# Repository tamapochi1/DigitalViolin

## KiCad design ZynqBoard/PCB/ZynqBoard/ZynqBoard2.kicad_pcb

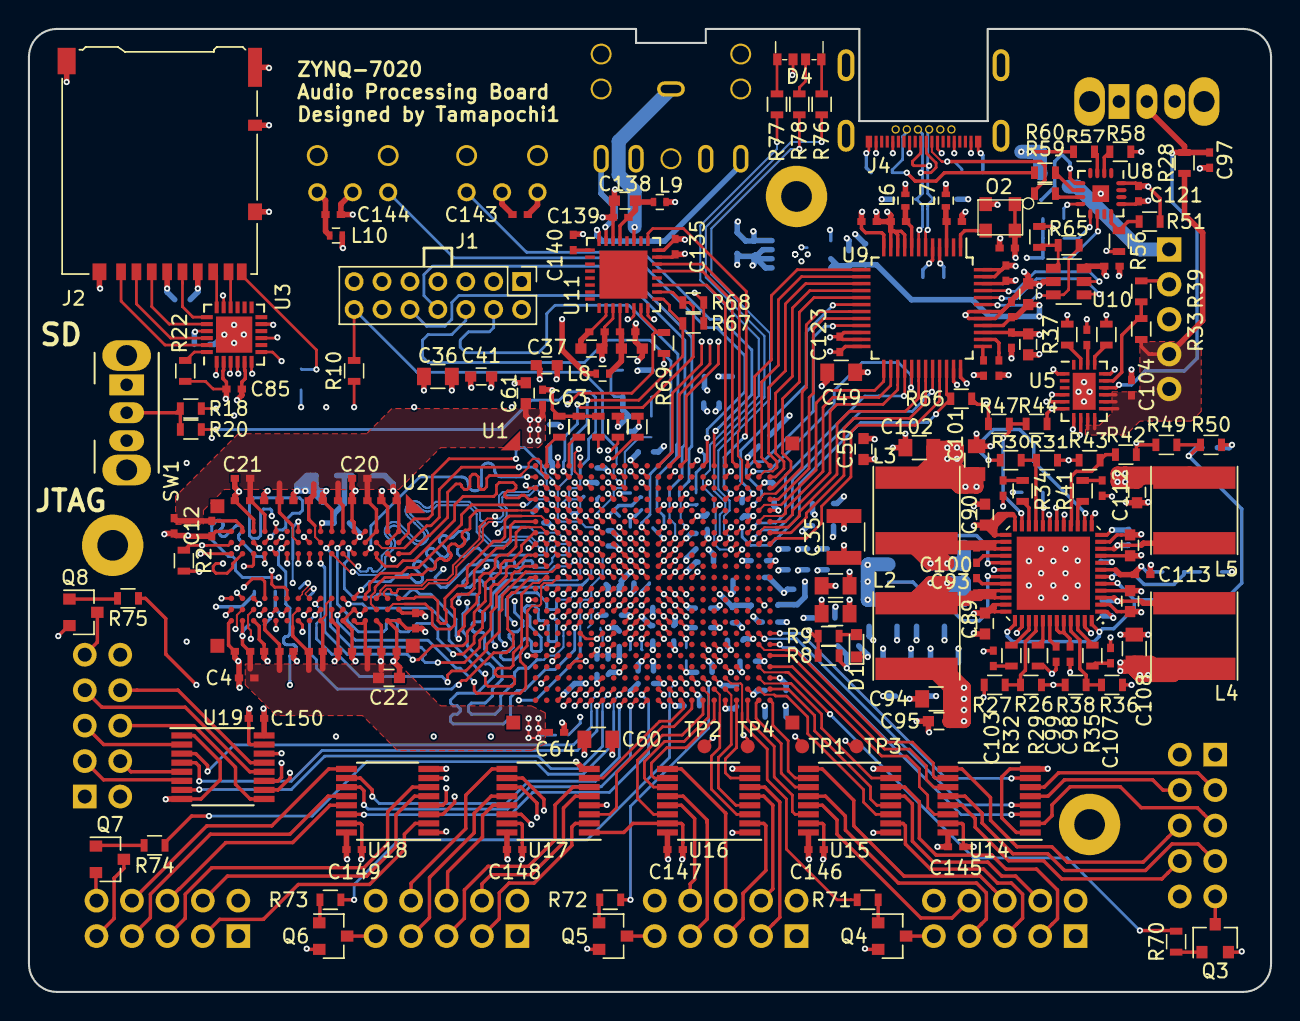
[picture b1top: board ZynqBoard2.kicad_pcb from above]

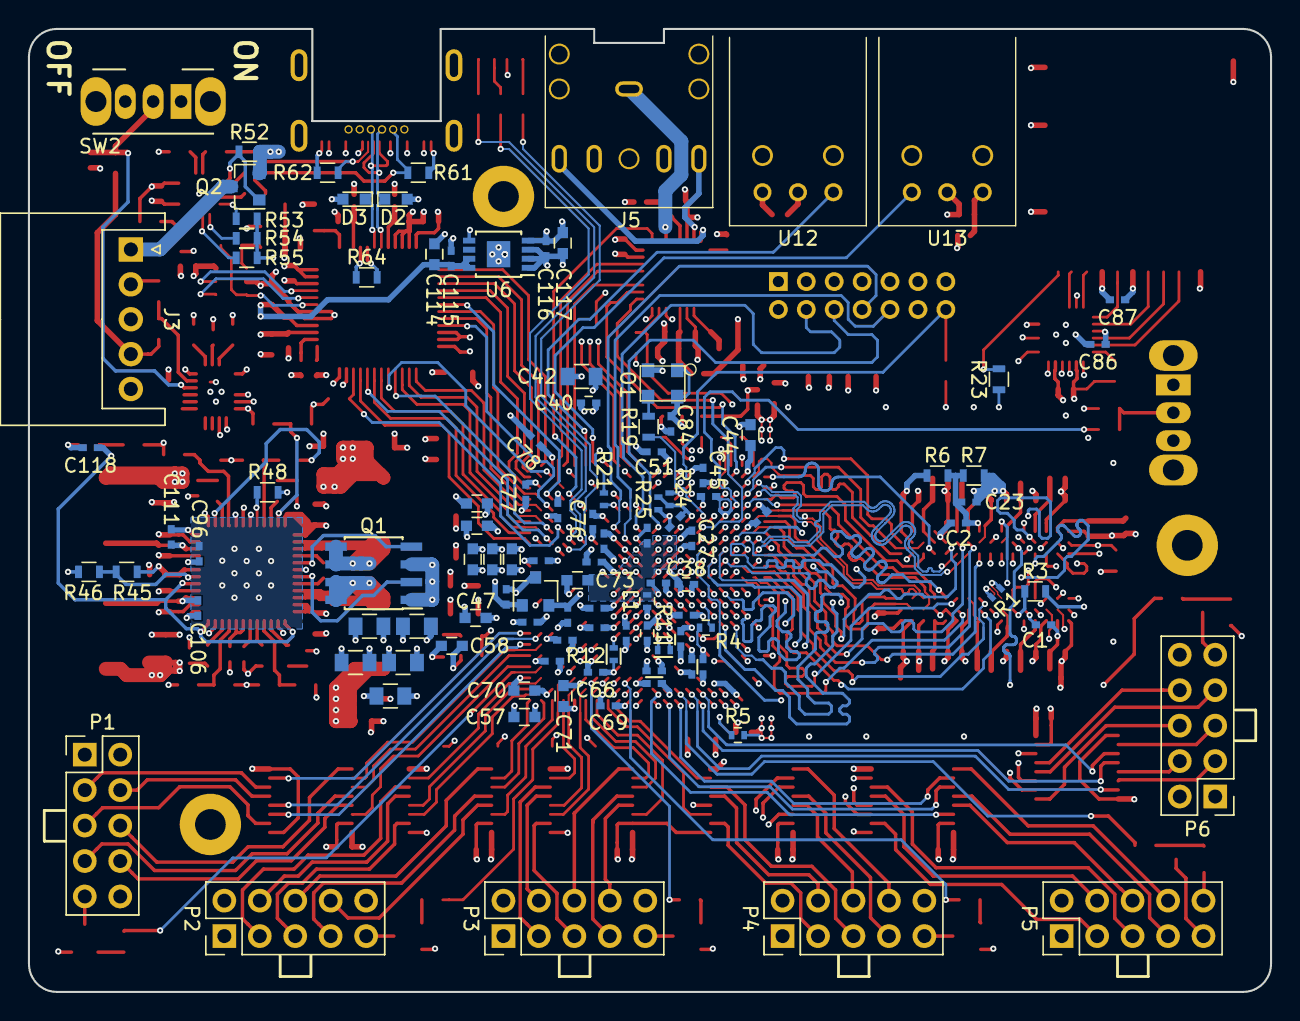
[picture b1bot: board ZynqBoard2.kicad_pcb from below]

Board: 6 copper layers, 89.0 x 69.0 mm, 288 parts (108 on the bottom side), 295 nets.

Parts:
C1, C2, C23, C88, C109: 10n; C_0402_NoSilk
C3, C82, C83, C84, C85, C86, C87, C93, C100, C104, C106, C111, C115, C116, C119, C120, C122, C123, C124, C126, C127, C128, C130, C131, C132, C133, C134, C135, C137, C139, C141, C143, C144, C145, C146, C147, C148, C149, C150: 0.1u; C_0402_NoSilk
C4, C5, C6, C7, C8, C9, C10, C11, C12, C13, C14, C15, C16, C17, C18, C19: 47n; C_0402_NoSilk
C20, C21, C26, C27, C28, C29, C30, C31, C32, C45, C46, C51, C53, C54, C55, C56, C62, C63, C64, C65, C66, C67, C68, C69, C74, C75, C76, C77, C78: 0.47u; C_0402_NoSilk
C22, C25, C33, C34, C37, C41, C44, C47, C50, C57, C58, C61, C70, C71, C79, C80, C95, C114, C117, C125, C129, C136, C138: 4.7u; C_0603
C24, C36, C43, C48, C49, C59, C60, C72, C81: 100u; C_0805
C35: 330u; C_1210
C38, C39, C40: 0.47u; C_0402
C42, C52, C94, C101, C102: 47u; C_0805
C73, C89, C90, C91, C92, C112: 10u; C_0603
C96, C97, C98, C99, C113, C121, C140: 1u; C_0402_NoSilk
C103, C105: 2.7n; C_0402_NoSilk
C107: 1n; C_0402_NoSilk
C108: 22u; C_0805
C110: 3.9n; C_0402_NoSilk
C118: 2.2n; C_0402_NoSilk
C142: 2.2u; C_0603
D1: DONE(BLUE); LED_0603
D2, D3: PGB1010603MR; LED_0603
D4: CL-425
J1: JTAG-HS3; Pin_Header_Straight_2x07_Pitch2.00mm
J2: Hirose_DM3AT; Hirose_DM3AT-SF-PEJM5
J3: Battery; JST_XH_S05B-XH-A_05x2.50mm_Angled
J4: USB_C_Receptacle; CX70M-24P1
J5: 35RAPC2BHN2; 35RAPC
L1, L6, L7, L8, L9, L10: 600ohm@100MHz; L_0402
L2, L3: 1.5uH; L_Taiyo-Yuden_NR-60xx
L4, L5: 3.3u; L_Taiyo-Yuden_NR-60xx
O1: DSC1001CI5-033.3333; DSC1001_CDFN-4_3.2x2.5
O2: DSC1001CL2-012.0000; DSC1001_CDFN-4_3.2x2.5
P1: Universal I/F 1; Pin_Header_Straight_2x05_Pitch2.54mm
P2: Universal I/F 2; Pin_Header_Straight_2x05_Pitch2.54mm
P3: Universal I/F 3; Pin_Header_Straight_2x05_Pitch2.54mm
P4: Universal I/F 4; Pin_Header_Straight_2x05_Pitch2.54mm
P5: Universal I/F 5; Pin_Header_Straight_2x05_Pitch2.54mm
P6: Universal I/F 6; Pin_Header_Straight_2x05_Pitch2.54mm
Q1: FDS9926A; SOIC-8_3.9x4.9mm_Pitch1.27mm
Q2: Si2369DS; SOT-23
Q3, Q4, Q5, Q6, Q7, Q8: IRLML6344TRPbF; SOT-23
R1: 80; R_0402_NoSilk
R2, R10, R22, R33, R34, R37, R47, R66, R69: 4.7k; R_0603
R3: 240; R_0603
R4, R5: 80; R_0402
R6, R7, R28, R31, R50, R53, R54, R55, R57, R58, R59, R60, R63: 10k; R_0603
R8, R39, R70, R71, R72, R73, R74, R75, R76, R77, R78: 1k; R_0603
R9: 220; R_0603
R11, R12: 4.7k; R_0402_NoSilk
R13, R14, R15, R16, R17, R18, R20, R40, R41, R44, R48, R52: 20k; R_0603
R19: 24; R_0603
R21: 40.2; R_0402_NoSilk
R23: 47k; R_0603
R24, R25: 10k; R_0402_NoSilk
R26, R43: 10.2k; R_0603
R27: 31.6k; R_0603
R29: 39.2k; R_0603
R30: 2.49k; R_0603
R32: 66.5k; R_0603
R35: 8.87k; R_0603
R36: 19.6k; R_0603
R38: 28.7k; R_0603
R42: 12.7k; R_0603
R45: 4.99k; R_0603
R46: 1.91k; R_0603
R49: 8.06k; R_0603
R51: 35.7k; R_0603
R56, R61, R62: 5.1k; R_0603
R64: 12k; R_0603
R65: 2k; R_0603
R67, R68: 3.3k; R_0603
SW1: Select_SD/JTAG; SW_CuK_OS102011MA1QN1_SPDT_Angled
SW2: SW_SPDT; SW_CuK_OS102011MA1QN1_SPDT_Angled
TP1: TEST1; Measurement_Point_Round-SMD-Pad_Small
TP2: TEST2; Measurement_Point_Round-SMD-Pad_Small
TP3: TEST3; Measurement_Point_Round-SMD-Pad_Small
TP4: TEST4; Measurement_Point_Round-SMD-Pad_Small
U1: XC7Z020-1CLG484C; BGA-484_22x22_19.0x19.0mm
U2: IS43TR16256AL-125KBL; BGA-96_2x3x16_9.0x13.0mm_Pitch0.8mm
U3: TXS02612RTWR; QFN-24-1EP_4x4mm_Pitch0.5mm
U4: ADP5052ACPZ-R7; LFCSP-VQ-48-1EP_7x7mm_Pitch0.5mm
U5: TPS25940ARVC; QFN-20-1EP_3x4mm_Pitch0.5mm
U6: ADP124ARHZ-3.3-R7; MSOP-8-1EP_3x3mm_Pitch0.65mm
U7: REF3012; SOT-23
U8: UTC2000; QFN-16-1EP_3x3mm_Pitch0.5mm
U9: FT-232H; LQFP-48_7x7mm_Pitch0.5mm
U10: 93LC56BT-I_OTCT; SOT-23-6
U11: AK4373EN; QFN-32-1EP_5x5mm_Pitch0.5mm
U12: PLT133_T10W; PLT133
U13: PLR135_T10; PLT133
U14, U15, U16, U17, U18, U19: M74HC365; TSSOP-16_4.4x5mm_Pitch0.65mm

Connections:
+1V0: C24.1, C25.1, C26.1, C27.1, C28.1, C29.1, C30.1, C31.1, C32.1, C33.1, C34.1, C35.1, C46.1, C47.1, C48.1, C101.1, C102.1, L3.1, R30.1, U1.G8, U1.H9, U1.H11, U1.J8, U1.J10, U1.J12, U1.J14, U1.K13, U1.L8, U1.L14, U1.M13, U1.N8, U1.N14, U1.P13, U1.R8, U1.R14, U4.14
+1V8: C36.1, C37.1, C38.1, C39.1, C40.1, C41.1, C42.1, C49.1, C50.1, C51.1, C85.1, C112.1, L1.1, L5.1, R10.1, R23.1, R24.1, R42.1, R49.1, R53.2, R54.2, R55.2, U1.A10, U1.B13, U1.D9, U1.E12, U1.G9, U1.K9, U1.L10, U1.M9, U1.N10, U1.P9, U1.P11, U1.R10, U1.T9, U3.5
+1V35: C1.1, C4.1, C5.1, C6.1, C7.1, C8.1, C9.1, C10.1, C11.1, C12.1, C13.1, C14.1, C15.1, C16.1, C17.1, C18.1, C19.1, C20.1, C21.1, C22.1, C60.1, C61.1, C62.1, C63.1, C64.1, C65.1, C108.1, L4.1, R5.2, R6.1, R36.1, U1.E2, U1.F5, U1.H1, U1.J4, U1.K7, U1.M3, U1.N6, U1.R2, U1.V1, U2.A1, U2.A8, U2.B2, U2.C1, U2.C9, U2.D2, U2.D9, U2.E9, U2.F1, U2.G7, U2.H2, U2.H9, U2.K2, U2.K8, U2.N1, U2.N9, U2.R1, U2.R9
+3.3VA: C122.1, C123.1, C124.1, C125.1, C126.1, C131.1, C133.1, L6.1, L7.1, O2.1, O2.4, R63.1, U9.12, U9.24, U9.39, U9.46, U10.6
+3V3: C43.1, C44.1, C45.1, C52.1, C53.1, C54.1, C55.1, C56.1, C57.1, C58.1, C59.1, C66.1, C67.1, C68.1, C69.1, C70.1, C71.1, C72.1, C75.1, C76.1, C77.1, C78.1, C79.1, C80.1, C81.1, C84.1, C86.1, C87.1, C94.1, C95.1, C96.1, C135.1, C143.1, C145.1, C146.1, C147.1, C148.1, C149.1, C150.1, D4.2, J1.2, J2.4, L2.2, L10.1, O1.1, O1.4, R8.1, R11.1, R12.2, R13.2, R27.2, R48.2, R67.1, R68.1, SW1.1, U1.A20, U1.AA10, U1.AA20, U1.AB3, U1.AB13, U1.B3, U1.C6, U1.C16, U1.D19, U1.E22, U1.F15, U1.G18, U1.H21, U1.R12, U1.T5, U1.T7, U1.T8, U1.T10, U1.T13, U1.U8, U1.U18, U1.V11, U1.V21, U1.W4, U1.W14, U1.Y7, U1.Y17, U3.17, U3.21, U4.8, U6.5, U11.6, U11.15, U12.2, U14.16, U15.16, U16.16, U17.16, U18.16, U19.16
+5V: C89.1, C90.1, C91.1, C92.1, C114.1, C115.1, C129.1, C130.1, P1.1, P2.1, P3.1, P4.1, P5.1, P6.1, R44.1, U4.4, U4.9, U4.24, U4.25, U4.35, U4.36, U5.4, U5.5, U5.6, U5.7, U5.8, U6.7, U6.8, U9.40
/Config/BOOT_MODE0: R18.1, U1.A3
/Config/BOOT_MODE1: R15.1, U1.F6
/Config/BOOT_MODE2: R20.1, U1.E4
/Config/BOOT_MODE3: R16.1, U1.A2
/Config/BOOT_MODE4: R17.1, U1.A4
/Config/DONE: R8.2, R9.1, U1.T12
/Config/PS_CLK: R19.2, U1.F7
/Config/TCK: J1.6, U1.G11
/Config/TDI: J1.10, U1.H13
/Config/TDO: J1.8, U1.G14
/Config/TMS: J1.4, U1.G12
/Config/VMODE0: R14.1, U1.D5
/Config/VMODE1: R13.1, U1.E5
/DDR/DDR_A0: U1.M4, U2.N3
/DDR/DDR_A1: U1.M5, U2.P7
/DDR/DDR_A2: U1.K4, U2.P3
/DDR/DDR_A3: U1.L4, U2.N2
/DDR/DDR_A4: U1.K6, U2.P8
/DDR/DDR_A5: U1.K5, U2.P2
/DDR/DDR_A6: U1.J7, U2.R8
/DDR/DDR_A7: U1.J6, U2.R2
/DDR/DDR_A8: U1.J5, U2.T8
/DDR/DDR_A9: U1.H5, U2.R3
/DDR/DDR_A10: U1.J3, U2.L7
/DDR/DDR_A11: U1.G5, U2.R7
/DDR/DDR_A12: U1.H4, U2.N7
/DDR/DDR_A13: U1.F4, U2.T3
/DDR/DDR_A14: U1.G4, U2.T7
/DDR/DDR_BA0: U1.L7, U2.M2
/DDR/DDR_BA1: U1.L6, U2.N8
/DDR/DDR_BA2: U1.M6, U2.M3
/DDR/DDR_CAS: U1.P3, U2.K3
/DDR/DDR_CKE: U1.V3, U2.K9
/DDR/DDR_CK_N: R1.2, U1.N5, U2.K7
/DDR/DDR_CK_P: R1.1, U1.N4, U2.J7
/DDR/DDR_CS: U1.P6, U2.L2
/DDR/DDR_DM0: U1.H3, U2.E7
/DDR/DDR_DM1: U1.B1, U2.D3
/DDR/DDR_DQ0: U1.G2, U2.E3
/DDR/DDR_DQ1: U1.L2, U2.F7
/DDR/DDR_DQ2: U1.J1, U2.F2
/DDR/DDR_DQ3: U1.L3, U2.F8
/DDR/DDR_DQ4: U1.G1, U2.H3
/DDR/DDR_DQ5: U1.L1, U2.H8
/DDR/DDR_DQ6: U1.K1, U2.G2
/DDR/DDR_DQ7: U1.K3, U2.H7
/DDR/DDR_DQ8: U1.E3, U2.D7
/DDR/DDR_DQ9: U1.D1, U2.C3
/DDR/DDR_DQ10: U1.E1, U2.C8
/DDR/DDR_DQ11: U1.D3, U2.C2
/DDR/DDR_DQ12: U1.F2, U2.A7
/DDR/DDR_DQ13: U1.C3, U2.A2
/DDR/DDR_DQ14: U1.F1, U2.B8
/DDR/DDR_DQ15: U1.B2, U2.A3
/DDR/DDR_DQS_0_N: U1.J2, U2.G3
/DDR/DDR_DQS_0_P: U1.H2, U2.F3
/DDR/DDR_DQS_1_N: U1.D2, U2.B7
/DDR/DDR_DQS_1_P: U1.C2, U2.C7
/DDR/DDR_DRST: R2.1, U1.F3, U2.T2
/DDR/DDR_ODT: U1.P5, U2.K1
/DDR/DDR_RAS: U1.R5, U2.J3
/DDR/DDR_VREF: C1.2, C2.1, C3.1, C23.1, R6.2, R7.1, U1.H7, U1.P7, U2.H1, U2.M8
/DDR/DDR_WE: U1.R4, U2.L3
/I/F/1_HRXD: P1.7, U14.12
/I/F/1_HSCK: P1.6, U14.9
/I/F/1_HTXD: P1.8, U14.13
/I/F/1_SRXD: P1.4, U14.5
/I/F/1_SSCK: P1.3, U14.6
/I/F/1_STXD: P1.5, U14.2
/I/F/2_HRXD: P2.7, U15.12
/I/F/2_HSCK: P2.6, U15.9
/I/F/2_HTXD: P2.8, U15.13
/I/F/2_SRXD: P2.4, U15.5
/I/F/2_SSCK: P2.3, U15.6
/I/F/2_STXD: P2.5, U15.2
/I/F/3_HRXD: P3.7, U16.12
/I/F/3_HSCK: P3.6, U16.9
/I/F/3_HTXD: P3.8, U16.13
/I/F/3_SRXD: P3.4, U16.5
/I/F/3_SSCK: P3.3, U16.6
/I/F/3_STXD: P3.5, U16.2
/I/F/4_HRXD: P4.7, U17.12
/I/F/4_HSCK: P4.6, U17.13
/I/F/4_HTXD: P4.8, U17.9
/I/F/4_SRXD: P4.4, U17.5
/I/F/4_SSCK: P4.3, U17.2
/I/F/4_STXD: P4.5, U17.6
/I/F/5_HRXD: P5.7, U18.12
/I/F/5_HSCK: P5.6, U18.13
/I/F/5_HTXD: P5.8, U18.9
/I/F/5_SRXD: P5.4, U18.5
/I/F/5_SSCK: P5.3, U18.2
/I/F/5_STXD: P5.5, U18.6
/I/F/6_HRXD: P6.7, U19.12
/I/F/6_HSCK: P6.6, U19.9
/I/F/6_HTXD: P6.8, U19.13
/I/F/6_SRXD: P6.4, U19.5
/I/F/6_SSCK: P6.3, U19.6
/I/F/6_STXD: P6.5, U19.2
/PL_IO/B: R78.1, U1.H18
/PL_IO/G: R77.1, U1.H19
/PL_IO/R: R76.1, U1.H17
/PL_IO/TEST1: TP1.1, U1.W18
/PL_IO/TEST2: TP2.1, U1.U16
/PL_IO/TEST3: TP3.1, U1.U17
/PL_IO/TEST4: TP4.1, U1.V17
/PowerSupply/SW_EN: C97.1, R28.2, SW2.2, U5.14
/PowerSupply/VREG: C98.1, U4.43, U4.44
/SD/SD_CD: J2.9, R23.2, U1.B10
/SD/SD_CLK: R21.1, U3.9
/SD/SD_CMD: U1.C8, U3.4
/SD/SD_D0: U1.D8, U3.6
/SD/SD_D1: U1.B11, U3.7
/SD/SD_D2: U1.E13, U3.1
/SD/SD_D3: U1.B9, U3.3
/SD/VREF0V9: C88.1, R24.2, R25.1, U1.F8
/USB/DM: D3.1, J4.A7, J4.B7, U9.6
/USB/DP: D2.1, J4.A6, J4.B6, U9.7
/USB/VPHY: C134.1, L7.2, U9.3
/USB/VPLL: C132.1, L6.2, U9.8
GND: C2.2, C3.2, C4.2, C5.2, C6.2, C7.2, C8.2, C9.2, C10.2, C11.2, C12.2, C13.2, C14.2, C15.2, C16.2, C17.2, C18.2, C19.2, C20.2, C21.2, C22.2, C23.2, C24.2, C25.2, C26.2, C27.2, C28.2, C29.2, C30.2, C31.2, C32.2, C33.2, C34.2, C35.2, C36.2, C37.2, C38.2, C39.2, C40.2, C41.2, C42.2, C43.2, C44.2, C45.2, C46.2, C47.2, C48.2, C49.2, C50.2, C51.2, C52.2, C53.2, C54.2, C55.2, C56.2, C57.2, C58.2, C59.2, C60.2, C61.2, C62.2, C63.2, C64.2, C65.2, C66.2, C67.2, C68.2, C69.2, C70.2, C71.2, C72.2, C73.2, C74.2, C75.2, C76.2, C77.2, C78.2, C79.2, C80.2, C81.2, C82.2, C83.2, C84.2, C85.2, C86.2, C87.2, C88.2, C89.2, C90.2, C91.2, C92.2, C94.2, C95.2, C96.2, C97.2, C98.2, C99.2, C101.2, C102.2, C103.1, C104.2, C105.1, C107.1, C108.2, C109.2, C110.1, C112.2, C113.2, C114.2, C115.2, C116.2, C117.2, C118.2, C119.2, C120.2, C121.2, C122.2, C123.2, C124.2, C125.2, C126.2, C127.2, C128.2, C129.2, C130.2, C131.2, C132.2, C133.2, C134.2, C135.2, C136.2, C137.2, C138.2, C139.2, C140.2, C141.2, C142.2, C143.2, C144.2, C145.2, C146.2, C147.2, C148.2, C149.2, C150.2, D1.1, D2.2, D3.2, J1.1, J1.3, J1.5, J1.7, J1.9, J1.11, J1.13, J2.6, J2.10, J2.11, J3.2, J3.3, J4.A1, J4.A12, J4.B1, J4.B12, J4.S1, O1.2, O2.2, P1.2, P1.10, P2.2, P2.10, P3.2, P3.10, P4.2, P4.10, P5.2, P5.10, P6.2, P6.10, Q1.1, Q1.3, Q3.2, Q4.2, Q5.2, Q6.2, Q7.2, Q8.2, R2.2, R3.2, R4.2, R7.2, R14.2, R15.2, R16.2, R17.2, R22.2, R25.2, R26.2, R29.1, R31.2, R37.2, R38.2, R39.2, R40.2, R43.2, R46.2, R47.2, R50.2, R56.2, R61.2, R62.2, R64.1, R66.2, R69.2, SW1.3, SW2.3, U1.A5, U1.A15, U1.AA5, U1.AA15, U1.AB8, U1.AB18, U1.B8, U1.B18, U1.C1, U1.C11, U1.C21, U1.D4, U1.D14, U1.E7, U1.E17, U1.F10, U1.F20, U1.G3, U1.H6, U1.H8, U1.H12, U1.H14, U1.H16, U1.J9, U1.J11, U1.J13, U1.J19, U1.K2, U1.K8, U1.K10, U1.K12, U1.K14, U1.K22, U1.L5, U1.L9, U1.L11, U1.L12, U1.L13, U1.L15, U1.M8, U1.M10, U1.M12, U1.M14, U1.M18, U1.N1, U1.N9, U1.N11, U1.N12, U1.N13, U1.N21, U1.P4, U1.P8, U1.P10, U1.P12, U1.P14, U1.R9, U1.R11, U1.R13, U1.R17, U1.T20, U1.U3, U1.U13, U1.V6, U1.V16, U1.W9, U1.W19, U1.Y2, U1.Y12, U1.Y22, U2.A9, U2.B1, U2.B3, U2.B9, U2.D1, U2.D8, U2.E1, U2.E2, U2.E8, U2.F9, U2.G1, U2.G8, U2.G9, U2.J2, U2.J8, U2.M1, U2.M9, U2.P1, U2.P9, U2.T1, U2.T9, U3.2, U3.11, U3.25, U4.2, U4.11, U4.13, U4.17, U4.18, U4.19, U4.30, U4.38, U4.47, U4.49, U5.1, U5.16, U5.21, U6.4, U6.9, U7.3, U8.13, U8.17, U9.4, U9.9, U9.10, U9.11, U9.22, U9.23, U9.35, U9.36, U9.41, U9.42, U9.47, U9.48, U10.2, U11.3, U11.8, U11.16, U11.22, U12.3, U13.2, U14.1, U14.8, U14.15, U15.1, U15.8, U15.15, U16.1, U16.8, U16.15, U17.1, U17.8, U17.15, U18.1, U18.8, U18.15, U19.1, U19.8, U19.15
HP_3V3: C116.1, C117.1, L8.1, L9.1, U6.1, U6.2, U6.3
HP_BCLK: U1.C19, U11.14
HP_LRCK: U1.A19, U11.13
HP_MCLK: U1.D18, U11.17
HP_RSTN: R69.1, U1.C5, U11.7
HP_SCL: R67.2, U1.G7, U11.9
HP_SDA: R68.2, U1.B4, U11.10
HP_SDT: U1.A18, U11.11
IF1_HRXD: U1.V22, U14.11
IF1_HSCK: U1.U21, U14.10
IF1_HTXD: U1.W22, U14.14
IF1_RST: R70.1, U1.W21
IF1_SRXD: U1.T21, U14.4
IF1_SSCK: U1.T22, U14.7
IF1_STXD: U1.U22, U14.3
IF2_HRXD: U1.AB21, U15.11
IF2_HSCK: U1.AB22, U15.10
IF2_HTXD: U1.AB20, U15.14
IF2_RST: R71.1, U1.Y18
IF2_SRXD: U1.AA22, U15.4
IF2_SSCK: U1.Y21, U15.7
IF2_STXD: U1.AA21, U15.3
IF3_HRXD: U1.AA16, U16.11
IF3_HSCK: U1.AB17, U16.10
IF3_HTXD: U1.AB16, U16.14
IF3_RST: R72.1, U1.Y16
IF3_SRXD: U1.AA18, U16.4
IF3_SSCK: U1.AB19, U16.7
IF3_STXD: U1.AA17, U16.3
IF4_HRXD: U1.Y14, U17.11
IF4_HSCK: U1.AA14, U17.14
IF4_HTXD: U1.AA13, U17.10
IF4_RST: R73.1, U1.Y13
IF4_SRXD: U1.Y15, U17.4
IF4_SSCK: U1.AB15, U17.3
IF4_STXD: U1.AB14, U17.7
IF5_HRXD: U1.AB10, U18.11
IF5_HSCK: U1.AA11, U18.14
IF5_HTXD: U1.AB9, U18.10
IF5_RST: R74.1, U1.AA9
IF5_SRXD: U1.AA12, U18.4
IF5_SSCK: U1.AB12, U18.3
IF5_STXD: U1.AB11, U18.7
IF6_HRXD: U1.AA6, U19.11
IF6_HSCK: U1.AB6, U19.10
IF6_HTXD: U1.AB5, U19.14
IF6_RST: R75.1, U1.AB4
IF6_SRXD: U1.AB7, U19.4
IF6_SSCK: U1.AA8, U19.7
IF6_STXD: U1.AA7, U19.3
unnamed: C73.1, C74.1, L1.2, U1.H10
unnamed: C93.1, U4.32
unnamed: C93.2, L2.1, Q1.7, Q1.8, U4.33, U4.34
unnamed: C99.1, U4.42
unnamed: C100.1, L3.2, Q1.5, Q1.6, U4.26, U4.27
unnamed: C100.2, U4.28
unnamed: C103.2, R32.1
unnamed: C105.2, R34.1
unnamed: C106.1, U4.1
unnamed: C106.2, L4.2, U4.3
unnamed: C107.2, R35.1
unnamed: C109.1, U5.18
unnamed: C110.2, R41.1
unnamed: C111.1, U4.12
unnamed: C111.2, L5.2, U4.10
unnamed: C118.1, R49.2, R50.1, U4.5, U4.37, U4.48
unnamed: C121.1, J4.A4, J4.A9, J4.B4, J4.B9, Q2.2, R51.1, R52.1, R57.1, R58.1, U8.16
unnamed: C127.1, U9.38
unnamed: C128.1, U9.37
unnamed: C136.1, C137.1, L8.2, U11.4
unnamed: C138.1, C139.1, L9.2, U11.21
unnamed: C140.1, U11.25
unnamed: C141.1, C142.1, U11.2
unnamed: C144.1, L10.2, U13.1
unnamed: D1.2, R9.2
unnamed: D4.1, R77.2
unnamed: D4.3, R78.2
unnamed: D4.4, R76.2
unnamed: J2.1, U3.23
unnamed: J2.2, U3.22
unnamed: J2.3, U3.20
unnamed: J2.5, U3.19
unnamed: J2.7, U3.18
unnamed: J2.8, U3.16
unnamed: J3.1, Q2.3
unnamed: J4.A5, R59.1, R62.1
unnamed: J4.B5, R60.1, R61.1
unnamed: J5.1, U11.19
unnamed: J5.2, U11.24
unnamed: J5.3, U11.23
unnamed: O1.3, R19.1
unnamed: O2.3, U9.1
unnamed: P1.9, Q3.3
unnamed: P2.9, Q4.3
unnamed: P3.9, Q5.3
unnamed: P4.9, Q6.3
unnamed: P5.9, Q7.3
unnamed: P6.9, Q8.3
unnamed: Q1.2, U4.31
unnamed: Q1.4, U4.29
unnamed: Q2.1, R52.2, U8.5
unnamed: Q3.1, R70.2
unnamed: Q4.1, R71.2
unnamed: Q5.1, R72.2
unnamed: Q6.1, R73.2
unnamed: Q7.1, R74.2
unnamed: Q8.1, R75.2
unnamed: R3.1, U2.L8
unnamed: R4.1, U1.N7
unnamed: R5.1, U1.M7
unnamed: R11.2, U1.T11
unnamed: R12.1, U1.T14
unnamed: R18.2, R20.2, SW1.2
unnamed: R21.2, U1.E14
unnamed: R22.1, U3.24
unnamed: R26.1, R27.1, U4.40
unnamed: R29.2, U4.41
unnamed: R30.2, R31.1, U4.21
unnamed: R32.2, U4.39
unnamed: R33.2, R39.1, U5.15
unnamed: R34.2, U4.22
unnamed: R35.2, U4.46
unnamed: R36.2, R38.1, U4.45
unnamed: R37.1, U5.19
unnamed: R40.1, U5.17
unnamed: R41.2, U4.15
unnamed: R42.2, R43.1, U4.16
unnamed: R44.2, R47.1, U4.23
unnamed: R45.2, R46.1, U4.6
unnamed: R51.2, R56.1, U8.12
unnamed: R57.2, U8.3
unnamed: R58.2, U8.2
unnamed: R59.2, U8.7
unnamed: R60.2, U8.6
unnamed: R63.2, R65.1, U10.1
unnamed: R64.2, U9.5
unnamed: R65.2, U9.43, U10.3
unnamed: U9.44, U10.4
unnamed: U9.45, U10.5
PG_ALL: R48.1, U1.B5, U4.20
PS_SRST_B: J1.14, R10.2, U1.C9
SPDIF_IN: U1.A16, U13.3
SPDIF_OUT: U1.A17, U12.1
USB_CBUS7: U1.G22, U9.31
USB_CBUS8: U1.H20, U9.32
USB_CBUS9: U1.H22, U9.33
USB_CLK60: U1.B20, U9.29
USB_DBUS0: U1.A21, U9.13
USB_DBUS1: U1.A22, U9.14
USB_DBUS2: U1.B21, U9.15
USB_DBUS3: U1.B22, U9.16
USB_DBUS4: U1.C22, U9.17
USB_DBUS5: U1.D20, U9.18
USB_DBUS6: U1.D21, U9.19
USB_DBUS7: U1.D22, U9.20
USB_OE#: U1.G21, U9.30
USB_RD#: U1.F21, U9.26
USB_RSTN: R66.1, U1.G19, U9.34
USB_RXF#: U1.E20, U9.21
USB_SIWU#: U1.G20, U9.28
USB_TXE#: U1.E21, U9.25
USB_WR#: U1.F22, U9.27
VBUS_0.5A: R53.1, U1.A12, U8.8
VBUS_1.5A: R54.1, U1.A13, U8.9
VBUS_3.0A: R55.1, U1.A14, U8.10
VIN: C104.1, J3.4, J3.5, R28.1, R33.1, U5.9, U5.10, U5.11, U5.12, U5.13
XADC_1V8: C82.1, C113.1, C119.1, R45.1, U1.K11, U4.7, U7.1
XADC_1V25: C83.1, C120.1, U1.M11, U7.2

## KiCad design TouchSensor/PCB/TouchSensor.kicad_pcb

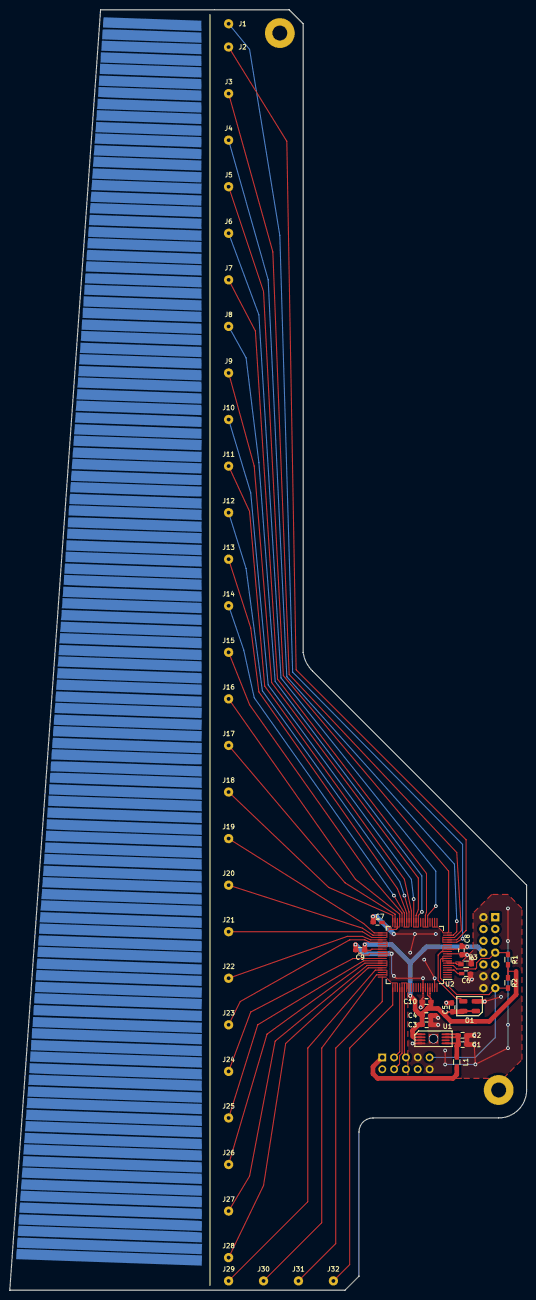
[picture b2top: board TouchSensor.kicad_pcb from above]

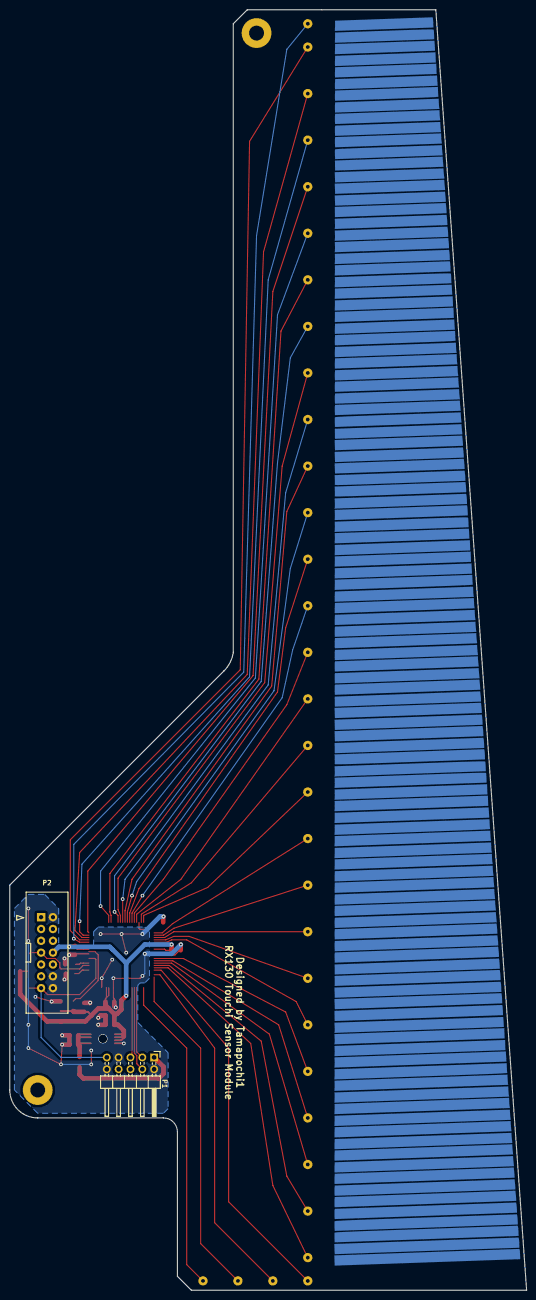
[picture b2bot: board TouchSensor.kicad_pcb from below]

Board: 2 copper layers, 111.0 x 275.0 mm, 51 parts (2 on the bottom side), 45 nets.

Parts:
C1, C4, C6: 4.7u; C_0603_HandSoldering
C2, C3, C5, C8, C9, C10: 0.1u; C_0603_HandSoldering
C7: 10n; C_0603_HandSoldering
J1: TS0; SolderWirePad_single_0-8mmDrill
J2: TS1; SolderWirePad_single_0-8mmDrill
J3: TS2; SolderWirePad_single_0-8mmDrill
J4: TS3; SolderWirePad_single_0-8mmDrill
J5: TS4; SolderWirePad_single_0-8mmDrill
J6: TS5; SolderWirePad_single_0-8mmDrill
J7: TS6; SolderWirePad_single_0-8mmDrill
J8: TS7; SolderWirePad_single_0-8mmDrill
J9: TS8; SolderWirePad_single_0-8mmDrill
J10: TS9; SolderWirePad_single_0-8mmDrill
J11: TS10; SolderWirePad_single_0-8mmDrill
J12: TS11; SolderWirePad_single_0-8mmDrill
J13: TS12; SolderWirePad_single_0-8mmDrill
J14: TS13; SolderWirePad_single_0-8mmDrill
J15: TS14; SolderWirePad_single_0-8mmDrill
J16: TS15; SolderWirePad_single_0-8mmDrill
J17: TS16; SolderWirePad_single_0-8mmDrill
J18: TS17; SolderWirePad_single_0-8mmDrill
J19: TS18; SolderWirePad_single_0-8mmDrill
J20: TS19; SolderWirePad_single_0-8mmDrill
J21: TS20; SolderWirePad_single_0-8mmDrill
J22: TS21; SolderWirePad_single_0-8mmDrill
J23: TS22; SolderWirePad_single_0-8mmDrill
J24: TS27; SolderWirePad_single_0-8mmDrill
J25: TS28; SolderWirePad_single_0-8mmDrill
J26: TS29; SolderWirePad_single_0-8mmDrill
J27: TS30; SolderWirePad_single_0-8mmDrill
J28: TS31; SolderWirePad_single_0-8mmDrill
J29: TS32; SolderWirePad_single_0-8mmDrill
J30, J31: TS33; SolderWirePad_single_0-8mmDrill
J32: TS34; SolderWirePad_single_0-8mmDrill
L1: BLM18KG331BH1D; L_0603_HandSoldering
O1: DSC1001CL5-008.0000T; 4-CDFN_3.2x2.5mm
P1: Conn_Universal; Pin_Header_Angled_2x05_Pitch2.54mm
P2: Conn_JTAG; JTAG
R1, R2, R3: 4.7k; R_0603_HandSoldering
U1: ADP124ARHZ-3.3-R7; 8-MSOP-EP_0.65mm
U2: R5F51303ADFN; QFP-80_12x12_Pitch0.5mm

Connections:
+3V3: C3.2, C4.2, C5.2, C8.2, C9.2, C10.2, O1.1, O1.4, P2.8, R1.1, R2.1, U1.1, U1.2, U1.3, U2.13, U2.48, U2.76, U2.77
+5V: L1.2, P1.1
/CLK8: O1.3, U2.12
/FINED: P2.7, R1.2, U2.6
/RES#: P1.9, P2.13, R2.2, U2.9
GND: C1.1, C2.1, C3.1, C4.1, C5.1, C6.2, C7.1, C8.1, C9.1, C10.1, O1.2, P1.2, P1.7, P1.10, P2.2, P2.12, P2.14, R3.2, U1.4, U1.EP, U2.11, U2.50, U2.74, U2.79
unnamed: C1.2, C2.2, L1.1, U1.5, U1.7, U1.8
unnamed: C6.1, U2.4
unnamed: C7.2, U2.38
unnamed: J1.1, U2.16
unnamed: J2.1, U2.17
unnamed: J3.1, U2.18
unnamed: J4.1, U2.19
unnamed: J5.1, U2.20
unnamed: J6.1, U2.25
unnamed: J7.1, U2.26
unnamed: J8.1, U2.29
unnamed: J9.1, U2.30
unnamed: J10.1, U2.31
unnamed: J11.1, U2.32
unnamed: J12.1, U2.33
unnamed: J13.1, U2.34
unnamed: J14.1, U2.35
unnamed: J15.1, U2.36
unnamed: J16.1, U2.37
unnamed: J17.1, U2.39
unnamed: J18.1, U2.40
unnamed: J19.1, U2.41
unnamed: J20.1, U2.42
unnamed: J21.1, U2.43
unnamed: J22.1, U2.44
unnamed: J23.1, U2.45
unnamed: J24.1, U2.52
unnamed: J25.1, U2.53
unnamed: J26.1, U2.54
unnamed: J27.1, U2.55
unnamed: J28.1, U2.56
unnamed: J29.1, U2.57
unnamed: J30.1, U2.59
unnamed: J31.1, U2.60
unnamed: J32.1, U2.61
unnamed: P1.3, U2.64
unnamed: P1.4, U2.65
unnamed: P1.5, U2.66
unnamed: R3.1, U2.7

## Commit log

2018-08-24 :boom::camel: Added .gitattributes
2018-08-24 Created TouchSensor and ZynqBoard
2018-08-24 CTSUのモジュールストップを解除できないバグを除去
2018-08-27 CTSUの割り込みを許可
2018-08-28 CTSUの計測チャンネルの設定を修正
2018-08-28 周辺端子機能の設定を追加
2018-09-01 ZynqBoard PCB を追加
2018-09-14 ZynqBoard PCB 設計完了
2018-09-20 Vivado,SDKのプロジェクトを追加
2018-09-24 ZynqBoard Lチカ
2018-10-03 ZynqBoard サイン波出力
2018-10-03 gitignore変更
2018-10-03 gitignore変更によるコミット
2018-10-03 10/3定期コミット
2018-10-09 ZynqBoard シンセサイザ実装（タイミング要件を満たしていない）
2018-10-10 10/11定期コミット
2018-10-16 ZynqBoard シンセサイザのタイミング要件を解決
2018-10-17 タッチセンサモジュール シリアル通信実装
2018-10-18 10/19定期コミット
2018-10-20 10/20定期コミット
2018-10-20 10/20定期コミット２
2018-10-22 タッチセンサモジュール 評価プログラム実装 gitignore変更
2018-10-23 タッチセンサモジュール 評価プログラムのアルゴリズムを改善
2018-10-24 タッチセンサモジュール ZynqBoard上でタッチ判定ができるように実装 gitignore変更・追加
2018-10-24 タッチセンサモジュールで音階が出せるように実装
2018-10-25 Vivado インターフェースの定義をip_repoフォルダに移動
2019-01-19 インプリメンテーションのクリティカルエラーを処理
2019-05-25 vivadoバージョン変更 SPIマスタ実装 コールバック確認
2019-05-27 FFT実装 計算結果は出るがデータの書き込み動作があやしい
2019-05-27 FFTバグ除去 FFTの動作を確認
2019-05-30 6チャンネルでADC＆FFT実装 動作確認
2019-06-01 ADCチャンネル数を8に 動作未確認
2019-06-03 ADC 8チャンネルで動作確認 UART
2019-06-04 FFTデータサイズを1024から256へ変更
2019-06-04 ボーレートを最速に変更
2019-06-10 MiniZedに移植
2019-07-15 完成バージョン1
